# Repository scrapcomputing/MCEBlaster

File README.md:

# MCE Blaster

A versatile standalone MCA/CGA/EGA TTL to VGA adapter based on a raspberry pi Pico.

# Videos
- MCE Blaster video part 3: https://www.youtube.com/watch?v=SX1B-mfE6yk
- MCE Blaster video part 2: https://www.youtube.com/watch?v=Neg1WR7Hz5s
- MCE Blaster video part 1: https://www.youtube.com/watch?v=kgDOiGoxKvE

# What it does
The Pico reads the TTL input video signal, writes the pixels to a buffer and then generates the VGA signal using the pixels from the buffer.

# Features
- No need for a VGA up-scaler or a 15KHz VGA monitor. Works with standard VGA modes.
- Pixel-perfect output:
  - VGA 640x400 for CGA/EGA 320x200,640x200 and 640x350 inputs
  - VGA 800x600 for MDA 720x350
  - VGA 640x480 for vertical resolutions between 200 and 240
- Pixel clock tuning for each mode
- Auto-adjustment functionality that centers the image on screen
- EGA brown color correction
- On-screen menu and messages
- Through-Hole PCB

# Installing the firmware to the Pico (Pico 1 or Pico 2)
- Download firmware (MCEBlaster_pico1.uf2 or MCEBlaster_pico2.uf2): https://github.com/scrapcomputing/MCEBlaster/releases
- Unplug the Pico
- Press and hold the small "BOOTSEL" button on the Pico
- While holding the BOOTSEL button, connect the Pico to your PC with a micro-USB cable
- The Pico should show up as a mass-storage device
- Copy the `MCEBlaster_pico1.uf2` or `MCEBlaster_pico2.uf2` firmware to the drive associated with the Pico
- Safely eject the mass-storage device

# Usage

*NOTE: Controls have changed since version 0.2!*

## Adjusting the pixel clock
- Push the `PIXEL CLOCK` button once, this will enter the pixel adjust mode. This should show text on screen displaying the current pixel clock.
- Coarse adjustment:
  - Push `PIXEL CLOCK` to increment the pixel clock by 10KHz.
  - Push `AUTO ADJUST` to decrement the pixel clock by 10KHz.
- Fine adjustment:
  - Long-push (push until the push registers) `PIXEL CLOCK` to increment the pixel clock by 1 KHz.
  - Long-push (push until the push registers) `AUTO ADJUST` to decrement the pixel clock by 1 KHz.
  - Medium-push (about half a second push and release) `PIXEL CLOCK` to increment the sampling offset and then increment the pixel clock by 1 KHz once we have tried all offsets.
  - Medium-push (about half a second push and release) `AUTO ADJUST` to decrement the sampling offset and then decrement the pixel clock by 1 KHz once we have tried all offsets.
- Exit pixel clock adjust mode by not pushing any buttons for 12 seconds. This saves the settings to flash.

### Sampling Offset (since rev 0.3)
The sampling offset is a fine-tuning knob added in rev 0.3 that shifts TTL sampling to try to avoid sampling the pixels during the transitions (shown as `X`).
In this example, using a sampling offset of 1 will result in a very noisy image because sampling takes place during the pixel transitions.

```
                    _____ _____ _____ _____
TTL Pixels:        X_____X_____X_____X_____X
Sampling offset 0:      |     |     |     |
Sampling offset 1:       |     |     |     |
Sampling offset 2:        |     |     |     |
Sampling offset 3:         |     |     |     |

```

The reason why offsets are needed and a demonstration of how they work can be found in [video part 3](https://www.youtube.com/watch?v=SX1B-mfE6yk).

## Centering the image
- Push the `AUTO ADJUST` button. This works best when the image shown is full from border to border.

## Print TTL Info (since v0.2)
Long-pressing the `PIXEL CLOCK` button will show a screen with information about the TTL signal.
Note: this is not updated in real-time.

You can exit the screen by pushing any button.

## Manually Setting TTL Options (since v0.2)
By default the MCE Blaster will automatically detect the TTL mode by checking the VSync frequency and the VSync Polarity. If these match the standard MDA/CGA/EGA modes used in PCs this will usually work fine.

But since Version 0.2 the MCE Blaster also supports manually setting:
1. The mode (MDA/CGA/EGA),
2. The horizontal and vertical resolution
3. The horizontal and vertical screen offset (on the TTL side)
with the help of an on-screen menu.

The operation is straight forward:
- To enter the menu long-push both buttons for more than a second until the "MANUAL-TTL" menu shows up.
- The single-line menu consists of 4 items that can be modified. The one that can be currently modified is enclosed in square brackets `[<selected>]`. For example:
```
          Currently
          Selected      Horiz Offset  Vertical Offset
            vvv               vvv      vvv
MANUAL-TTL [CGA] 640 x 200 X: AUTO  Y: AUTO
   ^         ^   ^     ^
On/Off  TTL-mode Horiz x Vertical Resolution
```
the currently selected option is `CGA`.
- Change the value of the selected item with a short push of the buttons.
- Cycle through the items by long-pushing the buttons: one will cycle in one direction and the other in the opposite.
- The options are saved to flash when the user stops pushing buttons for 12 seconds.

## Reset to Factory Defaults (since v0.2)
Occasionally the user may save to flash some configuration that makes the MCE Blaster unusable or inoperable.
In this case you can reset to defaults by pressing both buttons while powering on the device.
Upon a successful reset you will see the LED blinking fast for about 2 seconds.
You can release the buttons after that and the MCE Blaster will start with the default settings.

## Profiles (since v0.3 beta13)
The MCE Blaster supports a number of profiles, which helps when swapping video cards.
The settings for one card can be at Profile 0, the settings for another card can be at Profile 1 etc.
The default profile is Profile 0.

Changing profiles is as easy as long-pressing the `AUTO ADJUST` button and cycling through the profiles with either the `AUTO ADJUST` or the `PIXEL CLOCK` button.

Profiles are demonstrated briefly in [video part 3](https://www.youtube.com/watch?v=SX1B-mfE6yk).

# How it works
## Overview
The first core reads the TTL video data (through the level-shifter) from a PIO state-machine and places the pixels onto a buffer in memory.
The second core works completely independently from the first core and reads the pixel from the buffer and feeds them, along with the necessary Horizontal and Vertical Sync signals to a PIO state machine that writes to GPIO outputs.
The output is converted to analogue with the help of a simple R-2R DAC consisting of two resistors.
Feel free to check out the [video part 1](https://www.youtube.com/watch?v=kgDOiGoxKvE) for a visual overview.

## PIO state machines
The PIO state machines are used not only receiving the TTL video data and writing the VGA video data, but also for other helper functions including:
- Detecting no input signal: This checks if the horizontal sync signal is active.
- Detecting the image offset: This counts the black border pixel until a non-black pixel is found across all lines. This count is used for centering the image automatically.
- The EGA PIO state machine also does the Brown pixel fix because the overhead of doing that in a CPU core was too high.

## Sampling clock
The TTL video input is read by a PIO state-machine (one version for each video mode).
But getting it to sample the pixels at the right time requires us adjust the sampling period in a precise way to match the TTL video card's internal pixel clock.
Using the PIO clock divider does not give us a good-enough precision, because the fractional part of the divider is an 8-bit number, meaning that we get precision of ~0.004ns, but what we really need is about 0.001ns.
So what we do is that we have multiple implementations of the state-machine code, each with a different sampling period and we look for the one that has the lowest division error using the PIO's 8-bit divider.
This process is explained in more detail in the [video part 2](https://www.youtube.com/watch?v=Neg1WR7Hz5s).

# PCB

# Schematic

# Bill Of Materials

Download gerbers: https://github.com/scrapcomputing/MCEBlaster/releases

*NOTE: You can still use the latest firmware with old revisions of the PCB, they are fully compatible.*

Reference      | Quantity     | Value                                                                  | Description
---------------|--------------|------------------------------------------------------------------------|------------
N/A            | 3            | 1K Rm065 through-hole linear potentiometer (optional: can be replaced by a wire between 2 pins as shown on PCB and the [photo below](#potentiometers-are-optional) | Adjust R G B VGA signals
C1             | 1            | 0.1uF disk ceramic capacitor                                           | Decoupling capacitor for level-shifter IC
D1             | 1 (optional) | Diode Through-hole (e.g., Schottky 1N5817 or silicon 1N4001)           | For powering the MCE Blaster from the PC (instead of the Pico's micro-USB)
J2             | 1 (optional) | 1x02 through-hole Male PinHeader 2.54mm                                | For alternative external power
J1             | 1            | DB9 Male Horizontal                                                    | For connecting to TTL video card
J3             | 1            | DB15 Female HighDensity Connector (e.g., Kycon K61X-E15S-NJ-VESA, thanks @wrljet) | For connecting to VGA monitor
R3 R4 R6       | 3            | 390 Ohm Through-hole resistor 1% (alternatively 470 Ohm)               | For VGA signal DAC
R2 R5 R7       | 3            | 780 Ohm Through-hole resistor 1% (alternatively 1K Ohm)                | For VGA signal DAC
SW1,SW2        | 2            | 6mm Through-hole push button                                           | Auto-adjust and pixel-clock buttons
U1             | 1            | 74LVC245A DIP-20 (e.g., SN74LVC245AN) (+ optional socket)              | Level-shifter IC (NOTE: in the video I am using an 74HCT245 which turns out operates [out of spec](https://github.com/scrapcomputing/MCEBlaster/issues/31))
U2             | 1            | RaspberryPi Pico (or Pico 2)                                           | Pi Pico (or Pico 2)
N/A (for Pico) | 2            | 1x20 female through-hole pin-header 2.54mm pitch                       | PCB Pico headers
N/A (for Pico) | 2            | 1x20 male through-hole pin-header 2.54mm pitch                         | Headers for the Pico

## Potentiometers are optional.

They can be replaced by a wire as shown in the photo:

# Build instructions (for developers)
## Requirements:
- C++17 cross compiler (see instructions in https://github.com/raspberrypi/pico-sdk)
- Pico-SDK 2.2.0 or later (https://github.com/raspberrypi/pico-sdk)
- cmake 3.13 or later

## Build for Pico (rp2040) or Pico 2 (rp2350)
```
$ cd firmware && mkdir build && cd build
$ cmake -DPICO_BOARD=<pico|pico2> -DCMAKE_BUILD_TYPE=Release -DPICO_FREQ=270000 -DPICO_SDK_PATH=<path-to-pico-sdk> ../src/
$ make -j
```

# Resources:
- https://minuszerodegrees.net/mda_cga_ega/mda_cga_ega.htm
- https://en.wikipedia.org/wiki/IBM_Monochrome_Display_Adapter
- https://en.wikipedia.org/wiki/Enhanced_Graphics_Adapter
- https://en.wikipedia.org/wiki/Color_Graphics_Adapter
- https://en.wikipedia.org/wiki/VGA_connector

# Similar Projects
- Necroware's [mce-adapter](https://github.com/necroware/mce-adapter)
- [RGBtoHDMI](https://github.com/hoglet67/RGBtoHDMI/wiki)

# Change Log
- Rev 0.1: Initial release.
- Rev 0.2: Major redesign. Manual TTL, menus show live background
- Rev 0.3: Better adjustment of pixel clock with sampling offset, support for Pico 2, and fix colors in some monitors

# License
The project is GPLv2.

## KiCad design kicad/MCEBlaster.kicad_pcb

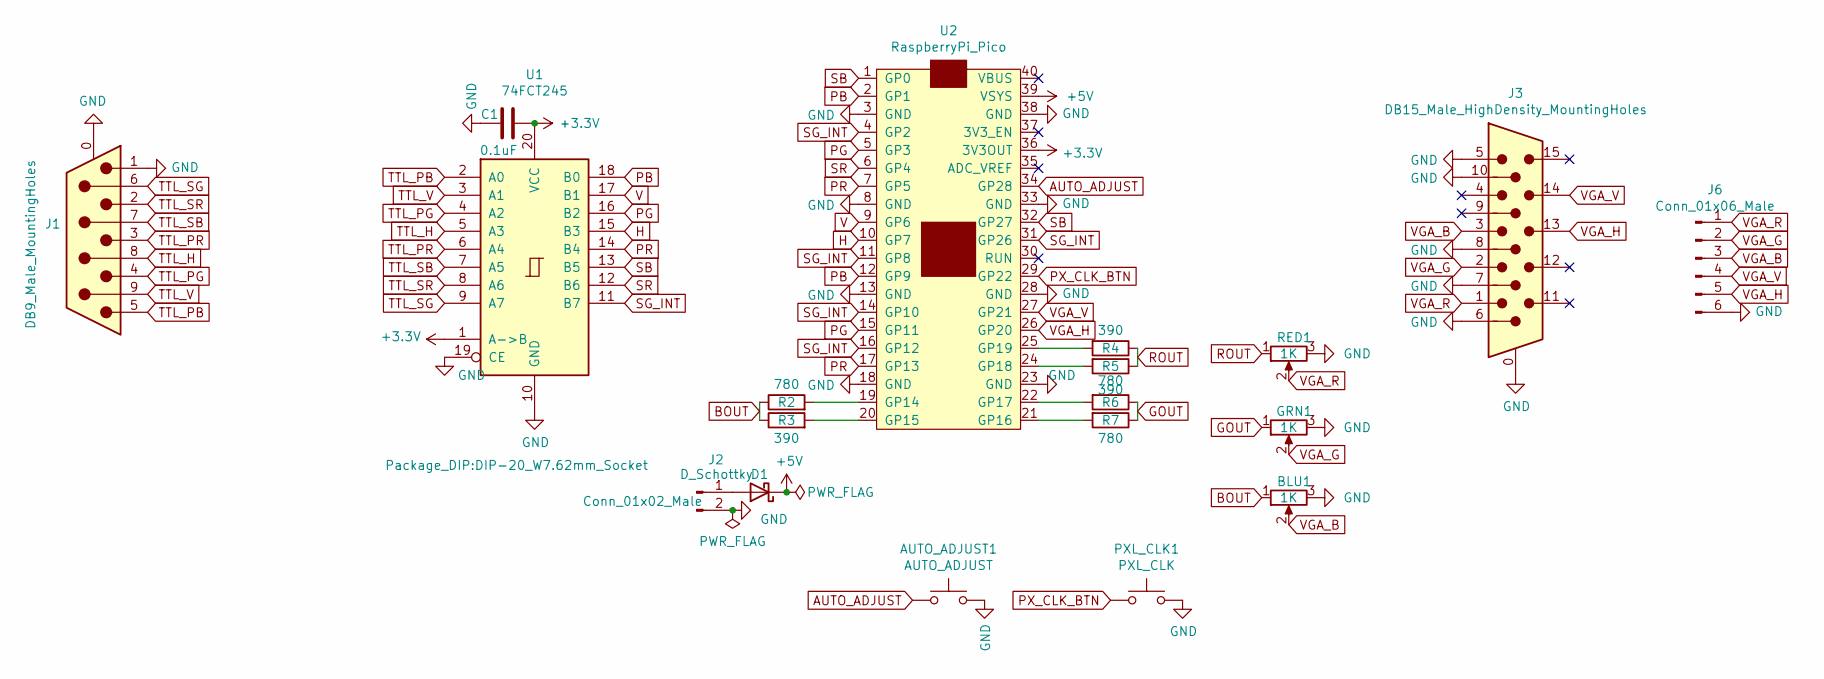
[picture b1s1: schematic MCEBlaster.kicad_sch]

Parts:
AUTO_ADJUST1: AUTO_ADJUST; SW_PUSH_6mm
BLU1: 1K; Potentiometer_Runtron_RM-065_Vertical
C1: 0.1uF; C_Disc_D4.3mm_W1.9mm_P5.00mm
D1: D_Schottky; D_A-405_P7.62mm_Horizontal
GRN1: 1K; Potentiometer_Runtron_RM-065_Vertical
J1: DB9_Male_MountingHoles; DSUB-9_Male_Horizontal_P2.77x2.84mm_EdgePinOffset4.94mm_Hou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
J2: Conn_01x02_Male; PinHeader_1x02_P2.54mm_Vertical
J3: DB15_Male_HighDensity_MountingHoles; VGA_connector_both_short_and_long
J6: Conn_01x06_Male; PinHeader_1x06_P2.54mm_Vertical
PXL_CLK1: PXL_CLK; SW_PUSH_6mm
R2, R5, R7: 780; R_Axial_DIN0207_L6.3mm_D2.5mm_P10.16mm_Horizontal
R3, R4, R6: 390; R_Axial_DIN0207_L6.3mm_D2.5mm_P10.16mm_Horizontal
RED1: 1K; Potentiometer_Runtron_RM-065_Vertical
U1: 74FCT245; DIP-20_W7.62mm_Socket
U2: RaspberryPi_Pico; raspberry_pi_pico

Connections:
+3V3: C1.1, U1.1 (A->B), U1.20 (VCC), U2.36 (3V3OUT)
+5V: D1.1 (K), U2.39 (VSYS)
AUTO_ADJUST: AUTO_ADJUST1.1, U2.34 (GP28)
BOUT: BLU1.1, R2.1, R3.1
GND: AUTO_ADJUST1.2, BLU1.3, C1.2, GRN1.3, J1.0 (PAD), J1.1, J2.2, J3.0, J3.5, J3.6, J3.7, J3.8, J3.10, J6.6, PXL_CLK1.2, RED1.3, U1.10 (GND), U1.19 (CE), U2.3 (GND), U2.8 (GND), U2.13 (GND), U2.18 (GND), U2.23 (GND), U2.28 (GND), U2.33 (GND), U2.38 (GND)
GOUT: GRN1.1, R6.1, R7.1
H: U1.15 (B3), U2.10 (GP7)
unnamed: D1.2 (A), J2.1
unnamed: R2.2, U2.19 (GP14)
unnamed: R3.2, U2.20 (GP15)
unnamed: R7.2, U2.21 (GP16)
unnamed: R6.2, U2.22 (GP17)
unnamed: R5.2, U2.24 (GP18)
unnamed: R4.2, U2.25 (GP19)
PB: U1.18 (B0), U2.2 (GP1), U2.12 (GP9)
PG: U1.16 (B2), U2.5 (GP3), U2.15 (GP11)
PR: U1.14 (B4), U2.7 (GP5), U2.17 (GP13)
PX_CLK_BTN: PXL_CLK1.1, U2.29 (GP22)
ROUT: R4.1, R5.1, RED1.1
SB: U1.13 (B5), U2.1 (GP0), U2.32 (GP27)
SG_INT: U1.11 (B7), U2.4 (GP2), U2.11 (GP8), U2.14 (GP10), U2.16 (GP12), U2.31 (GP26)
SR: U1.12 (B6), U2.6 (GP4)
TTL_H: J1.8, U1.5 (A3)
TTL_PB: J1.5, U1.2 (A0)
TTL_PG: J1.4, U1.4 (A2)
TTL_PR: J1.3, U1.6 (A4)
TTL_SB: J1.7, U1.7 (A5)
TTL_SG: J1.6, U1.9 (A7)
TTL_SR: J1.2, U1.8 (A6)
TTL_V: J1.9, U1.3 (A1)
V: U1.17 (B1), U2.9 (GP6)
VGA_B: BLU1.2, J3.3, J6.3
VGA_G: GRN1.2, J3.2, J6.2
VGA_H: J3.13, J6.5, U2.26 (GP20)
VGA_R: J3.1, J6.1, RED1.2
VGA_V: J3.14, J6.4, U2.27 (GP21)

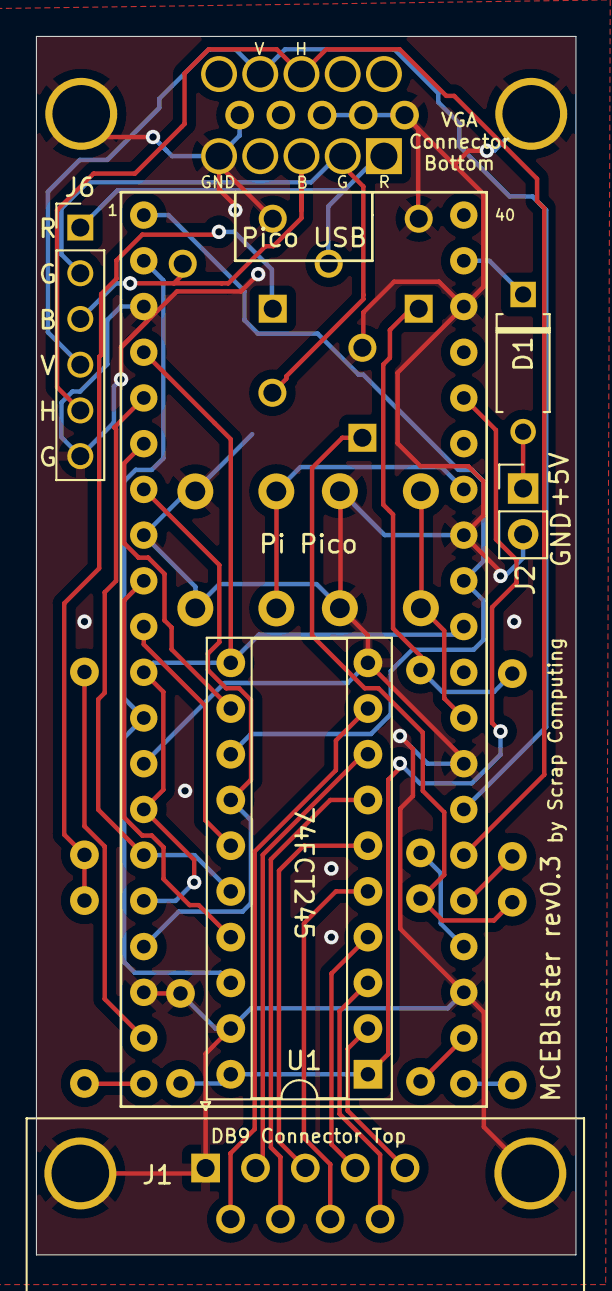
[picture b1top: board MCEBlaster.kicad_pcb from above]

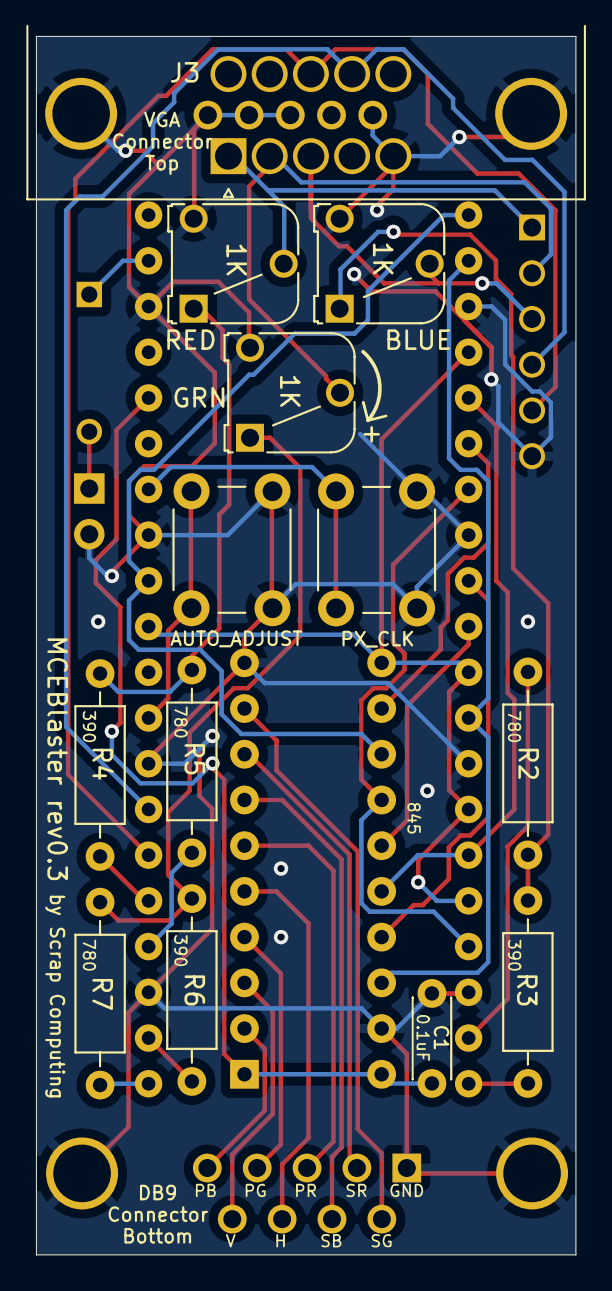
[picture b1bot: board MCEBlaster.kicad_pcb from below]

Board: 2 copper layers, 30.0 x 67.7 mm, 19 parts (13 on the bottom side), 36 nets.

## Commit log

2024-06-28 Rev 0.1
2024-06-28 README: Load firmware instructions
2024-06-29 README: Add schematic
2024-06-29 README: Add video link
2024-06-29 Fixed BOM IC part number to the correct 74LVC245
2024-06-30 Adds Through-hole PCB
2024-06-30 README: Adds the 'How it works' section
2024-10-11 Auto-adjust position is now saved to flash
2024-11-09 THT pcb updates
2024-11-09 Reduce flash frequency by default
    Some Picos, including many of the clones may not work when overclocked at 270MHz.
    The issue is usually the flash. This patch reduces the flash frequency by default.
    Many thanks to @emilen72 who looked into this.
2025-01-12 Fix CMakeLists.txt comment
2025-04-23 README: Add VGA connector part number in BOM (thanks @wrljet)
2025-05-31 Rev 0.2 beta: Major redesign and new features like Manual TTL
    - Auto-detect horizontal and vertical sync
    - Manual-TTL menu
    - Info TTL menu
    - On-screen menus no longer freeze the screen
    - Support VGA 640x480 and 640x400 for non-standard MDA
    - Reset to factory defaults
2025-05-31 Allow 520 visible lines in VGA 640x480 to help with 260-line TTL
2025-06-22 Rev 0.3: Adds sampling offset for better sampling
    Other changes:
    - ManualTTL allow negative X Y offsets
    - Fixes MDA image centering
2025-06-24 Increase MDA pixels by 32 more pixels and disable XBorder to fix horizontal offset issues
2025-06-24 Remove artifacts from bottom of screen that may show up when closing programs
2025-06-25 Lower flash frequency and mark performance critical functions as __not_in_flash_func
2025-06-29 Fix reading offsets from flash
2025-06-29 Add counter to delay displaying 'Unknown Message'
2025-07-13 Remove ADC and change cmake include path to fix missing hardware/flash.h build issue
2025-07-14 Fix linking error
2025-08-05 Pico 2 build
2025-09-11 Fix porch sizes which caused incorrect colors in some monitors
    Many thanks to @Bs0Dd for not only reporting the issue but also finding the root cause!
2025-09-14 Several bug fixes and improvements
    - Fix MDA display bug introduced in v0.3 beta 7
    - Fix MDA pixel clipping by making the MDA buffer even larger
    - Fix VGA sync pixels
    - Character bitmaps improvements
    - Fix mode switching bug from EGA 640x200 to 640x350
    - Fix vertical centering of EGA 640x350
2025-09-14 Fix Manual-TTL rotate-left selection
    Thanks @Bs0Dd for reporting the issue!
2025-09-14 Increase EGA max offset to 16
2025-09-14 PixelClock menu allow long-press
2025-09-14 Change XB to 16, YB to 0 and save memory by dropping char map
2025-09-16 Fix offset adjusting
2025-09-17 Rework the SamplingOffsetMod code
2025-09-17 Long-push changes the pixel clock by 1 KHz
2025-09-17 Increase EGA sampling offset to 25
2025-09-19 Change MDA sampling to be same as EGA to avoid any potential clipping
2025-09-19 Change CGA sampling to be same as EGA to avoid any potential clipping
2025-09-19 Finally fix EGA 640x350 horizontal clipping
2025-09-20 Reduce PORCH_ITER to 2 and increase sampling offset range for CGA and MDA.
2025-09-29 Add configuration profiles
2025-09-29 Replace std::vector with std::initializer_list in PioProgramLoader
2025-09-29 Utils::StaticString
2025-09-29 Replace std::vector with std::array in HorizMenu
2025-09-29 Replace std::map with FixedVector
2025-09-29 Replace std::vector with std::array in Buffer
2025-09-29 Replace std::vector with FixedVector
2025-10-01 Replace std::string with Utils::StaticString in HorizMenu
2025-10-04 Move functions from flash to mem
2025-10-05 Replace splash image with smaller to save memory (pico 1 only), performance tweaking, and +2 CGA sampling offsets
2025-10-05 Bug fix: med-push auto-adjust will now enter auto-adjust
    Thanks to @Bs0Dd for reporting the bug!
2025-10-25 PCB rev0.2
2025-10-25 PCB Rev 0.3
    Updates the VGA connector footprint. Should accept both "short" and "long" connectors.
2025-10-27 README: some more updates for rev 0.3
2025-11-06 README: Change the level-shifter model number
2026-03-16 Turn off VGA after 30s to avoid CRT burn-in
    Stop displaying the "No Signal" message after 30s and turn off the signals
    that drive the VGA. Some later CRT models should also enter low-power mode.
2026-03-16 Update revision numbering
2026-03-31 Add LICENSE file
2026-04-19 Update README, add screenshots
2026-04-25 Support pico2_w and pico_w
2026-04-26 Turn on the VGA signal when the user pushes a button
    When there is no TTL signal we turn off the VGA signal to save CRTs.
    If the user pushes a button we turn it back on again.
